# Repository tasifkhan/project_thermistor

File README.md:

## thermistor_array_driver

- Stream, visualize, and save 16 channel thermistor data using arduino due.
- The thermistor array is connected to the 32 pin .5 mm pitch FFC connector. Then, those connections goes to an analog switch, and to a bridge circuit.
- Switch address connections

| MUX Pins| Arduino Pins |
| :------:|:------------:|
| EN      |53            |
| A0      |51            |
| A1      |49            |
| A2      |47            |
| A3      |45            |

### directory setup

- /desktop_app/ ipython programs   and temperature and beta plot
  - 'temperature_mapping.ipynb' for real time temperature mapping
  - 'thermistor_array_plot_v1.ipynb' for thermistor temp and beta plots
- /desktop_app/data all raw data are saved here
- /firmware/ firmware for data streaming *use the latest version*
- /hardware/ hardware files

### notes

- 2017_09_13 added ipython real time temperature mapping and code for thermistor temp and beta plots
- 2017_08_27 checked both hardware and firmware, correctly outputting resistance values.

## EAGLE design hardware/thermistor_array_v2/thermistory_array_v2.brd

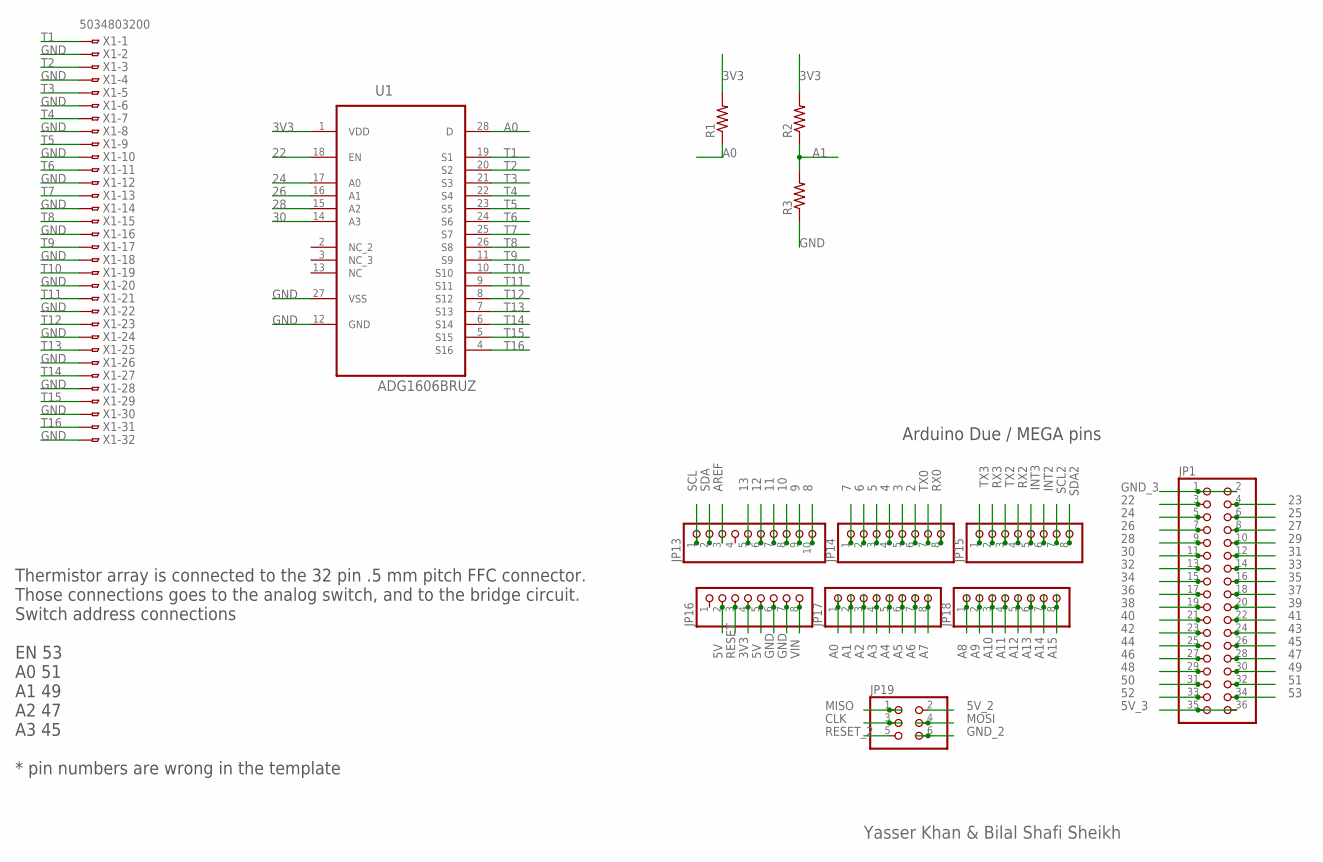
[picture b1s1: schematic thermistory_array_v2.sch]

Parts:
JP1: PINHD-2X18; 2X18
JP13: PINHD-1X10; 1X10
JP14, JP15, JP16, JP17, JP18: PINHD-1X8; 1X08
JP19: PINHD-2X3; 2X03
R1, R2, R3: RESISTORKIT; AXIAL-0.3-KIT
U1: ADG1606BRUZ; SOP65P640X120-28N
X1: 5034803200

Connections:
2: JP14.6
3: JP14.5
3V3: JP16.4, R1.P$2 (2), R2.P$2 (2), U1.1 (VDD)
4: JP14.4
5: JP14.3
5V: JP16.2, JP16.5
5V_2: JP19.2
5V_3: JP1.35, JP1.36
6: JP14.2
7: JP14.1
8: JP13.10
9: JP13.9
10: JP13.8
11: JP13.7
12: JP13.6
13: JP13.5
22: JP1.3, U1.18 (EN)
23: JP1.4
24: JP1.5, U1.17 (A0)
25: JP1.6
26: JP1.7, U1.16 (A1)
27: JP1.8
28: JP1.9, U1.15 (A2)
29: JP1.10
30: JP1.11, U1.14 (A3)
31: JP1.12
32: JP1.13
33: JP1.14
34: JP1.15
35: JP1.16
36: JP1.17
37: JP1.18
38: JP1.19
39: JP1.20
40: JP1.21
41: JP1.22
42: JP1.23
43: JP1.24
44: JP1.25
45: JP1.26
46: JP1.27
47: JP1.28
48: JP1.29
49: JP1.30
50: JP1.31
51: JP1.32
52: JP1.33
53: JP1.34
A0: JP17.1, R1.P$1 (1), U1.28 (D)
A1: JP17.2, R2.P$1 (1), R3.P$2 (2)
A2: JP17.3
A3: JP17.4
A4: JP17.5
A5: JP17.6
A6: JP17.7
A7: JP17.8
A8: JP18.1
A9: JP18.2
A10: JP18.3
A11: JP18.4
A12: JP18.5
A13: JP18.6
A14: JP18.7
A15: JP18.8
AREF: JP13.3
CLK: JP19.3
GND: JP16.6, JP16.7, R3.P$1 (1), U1.12 (GND), U1.27 (VSS), X1.2, X1.4, X1.6, X1.8, X1.10, X1.12, X1.14, X1.16, X1.18, X1.20, X1.22, X1.24, X1.26, X1.28, X1.30, X1.32
GND_2: JP19.6
GND_3: JP1.1, JP1.2
INT2: JP15.6
INT3: JP15.5
MISO: JP19.1
MOSI: JP19.4
RESET: JP16.3
RESET_2: JP19.5
RX0: JP14.8
RX2: JP15.4
RX3: JP15.2
SCL: JP13.1
SCL2: JP15.7
SDA: JP13.2
SDA2: JP15.8
T1: U1.19 (S1), X1.1
T2: U1.20 (S2), X1.3
T3: U1.21 (S3), X1.5
T4: U1.22 (S4), X1.7
T5: U1.23 (S5), X1.9
T6: U1.24 (S6), X1.11
T7: U1.25 (S7), X1.13
T8: U1.26 (S8), X1.15
T9: U1.11 (S9), X1.17
T10: U1.10 (S10), X1.19
T11: U1.9 (S11), X1.21
T12: U1.8 (S12), X1.23
T13: U1.7 (S13), X1.25
T14: U1.6 (S14), X1.27
T15: U1.5 (S15), X1.29
T16: U1.4 (S16), X1.31
TX0: JP14.7
TX2: JP15.3
TX3: JP15.1
VIN: JP16.8

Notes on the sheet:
Arduino Due / MEGA pins
Thermistor array is connected to the 32 pin .5 mm pitch FFC connector. Those connections goes to the analog switch, and to the bridge circuit. Switch address connections EN 53 A0 51 A1 49 A2 47 A3 45 * pin numbers are wrong in the template
Yasser Khan & Bilal Shafi Sheikh

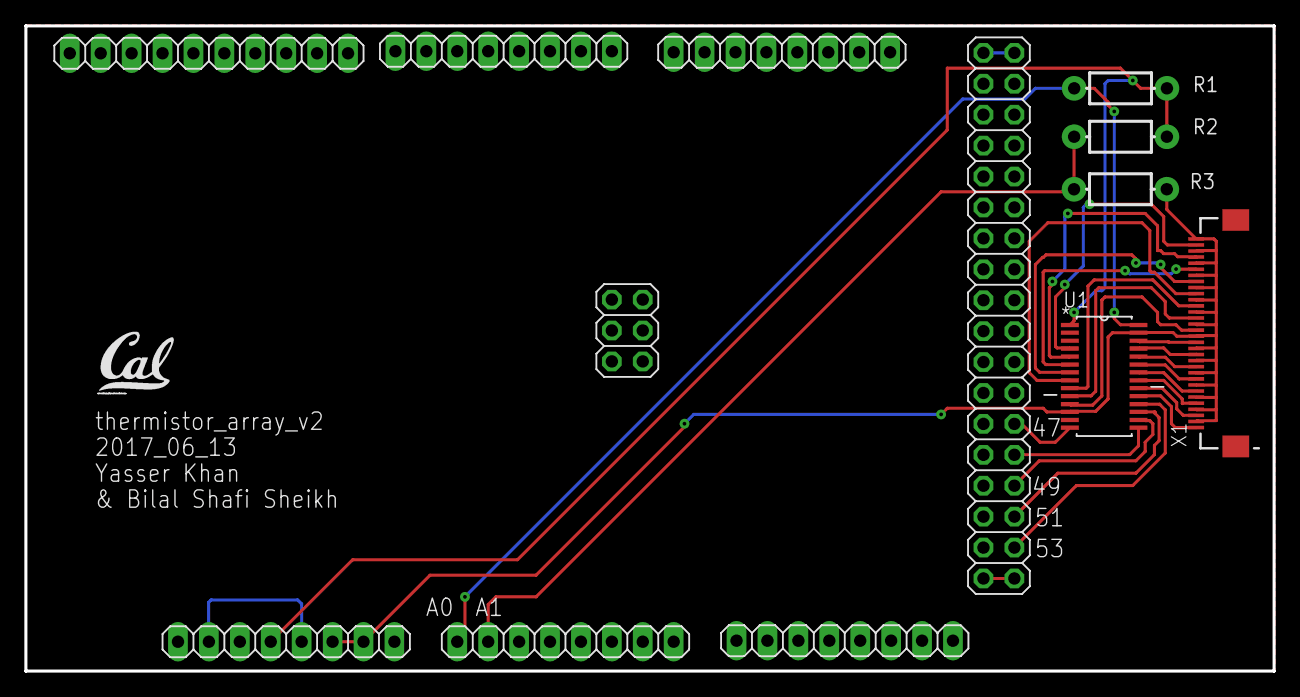
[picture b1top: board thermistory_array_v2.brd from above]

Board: 2 copper layers, 102.5 x 53.0 mm, 13 parts (0 on the bottom side), 28 nets.

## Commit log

2017-06-13 Initial commit.
2017-06-24 completed ard and proc programs
2017-07-17 added linear interpolation, must debug serial error
2017-07-18 new arduino stream
2017-07-18 mux added to the firmware
2017-08-30 hardware and firmware are working
2017-09-07 added ipython real time mapping
2017-09-10 added gitignore for data
2017-09-13 moved to the project_thermistor folder
2017-09-14 added code for mapping and plotting
2017-09-27 2017-09-26 update

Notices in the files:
parts and their libraries:
SparkFun-Passives: Licensing: Creative Commons ShareAlike 4.0 International - https://creativecommons.org/licenses/by-sa/4.0
